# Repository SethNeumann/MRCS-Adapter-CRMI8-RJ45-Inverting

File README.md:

# REPO NAME: EagleTemplate-new
## License: Creative Commons Attribution-NonCommercial-ShareAlike

The improved CMRI8-RJ45 adapter (with limiting resistor pads) AND an inverter

This version is aimed at CMRI users using common cathode signals and a logic true output.
It includes a 74HC540 octal latch inverter (but the latches are hardwared on) to source 
~ 8 mA @ 4V, which should be adequate for modern LEDs.  Other versions of 74xx540 will 
probably work as well as 74xx541 (non inverting) although I haven't tested them.

John Plocher did the original design based on a request from Jay Beckham, and later extended
it to support limiting resistors based on user requests.  Kris Puccinelli modified this 
design to include an octal inverter, but not on EAGLE.  This is an EAGLE version, designed
for panelization.

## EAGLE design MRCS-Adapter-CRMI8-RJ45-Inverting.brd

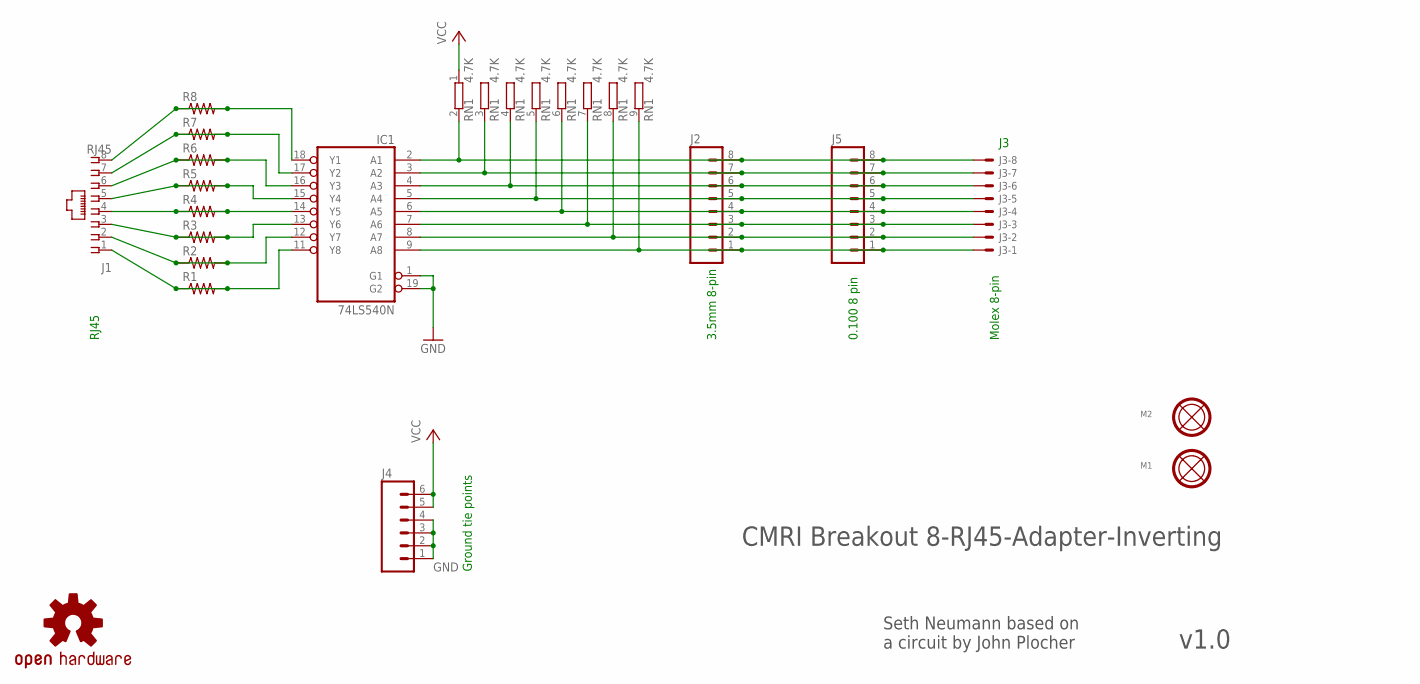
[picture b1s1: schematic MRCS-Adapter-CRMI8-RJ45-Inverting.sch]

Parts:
IC1: 74LS540N; DIL20
J1: RJ45; RJ45-NO-SHIELD
J2: CONNECTOR-M083.5MM-8; SCREWTERMINAL-3.5MM-8
J3: KK-156-8F; KK-156-8-F
J4: CONNECTOR-M06LOCK; 1X06_LOCK
J5: CONNECTOR-M08LOCK; 1X08_LOCK
M1, M2: MOUNTINGHOLE
R1, R2, R3, R4, R5, R6, R7, R8: RPTH04; AXIAL-0.4-RES
RN1: 4.7K; SIL9
U$1: DOC-OSHW-LOGO-L; OSHW-LOGO-L

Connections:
GND: IC1.1 (G1), IC1.10 (GND), IC1.19 (G2), J4.1, J4.2, J4.3, J4.4
L1: IC1.9 (A8), J2.1, J3.1, J5.1, RN1.9 (2)
L2: IC1.8 (A7), J2.2, J3.2, J5.2, RN1.8 (2)
L3: IC1.7 (A6), J2.3, J3.3, J5.3, RN1.7 (2)
L4: IC1.6 (A5), J2.4, J3.4, J5.4, RN1.6 (2)
L5: IC1.5 (A4), J2.5, J3.5, J5.5, RN1.5 (2)
L6: IC1.4 (A3), J2.6, J3.6, J5.6, RN1.4 (2)
L7: IC1.3 (A2), J2.7, J3.7, J5.7, RN1.3 (2)
L8: IC1.2 (A1), J2.8, J3.8, J5.8, RN1.2
unnamed: IC1.18 (Y1), J1.8, R8.P$1 (1), R8.P$2 (2)
unnamed: IC1.17 (Y2), J1.7, R7.P$1 (1), R7.P$2 (2)
unnamed: IC1.16 (Y3), J1.6, R6.P$1 (1), R6.P$2 (2)
unnamed: IC1.15 (Y4), J1.5, R5.P$1 (1), R5.P$2 (2)
unnamed: IC1.14 (Y5), J1.4, R4.P$1 (1), R4.P$2 (2)
unnamed: IC1.13 (Y6), J1.3, R3.P$1 (1), R3.P$2 (2)
unnamed: IC1.12 (Y7), J1.2, R2.P$1 (1), R2.P$2 (2)
unnamed: IC1.11 (Y8), J1.1, R1.P$1 (1), R1.P$2 (2)
VCC: IC1.20 (VCC), J4.5, J4.6, RN1.1

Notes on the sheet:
Molex 8-pin
3.5mm 8-pin
RJ45
v1.0
Ground tie points
CMRI Breakout 8-RJ45-Adapter-Inverting
Seth Neumann based on a circuit by John Plocher
0.100 8 pin

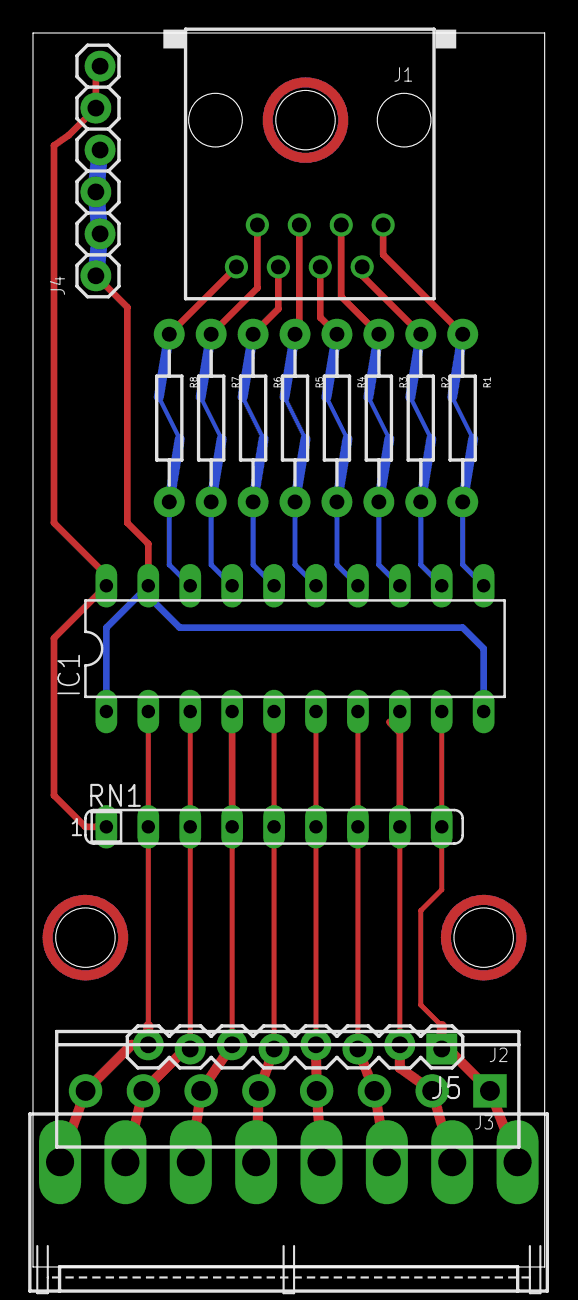
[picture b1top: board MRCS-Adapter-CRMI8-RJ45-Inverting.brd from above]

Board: 2 copper layers, 31.0 x 74.8 mm, 21 parts (0 on the bottom side), 18 nets.

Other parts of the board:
M3: MOUNTINGHOLE
U$2: CA-PROP65WARNING
U$3: MRCSLOGOBTM

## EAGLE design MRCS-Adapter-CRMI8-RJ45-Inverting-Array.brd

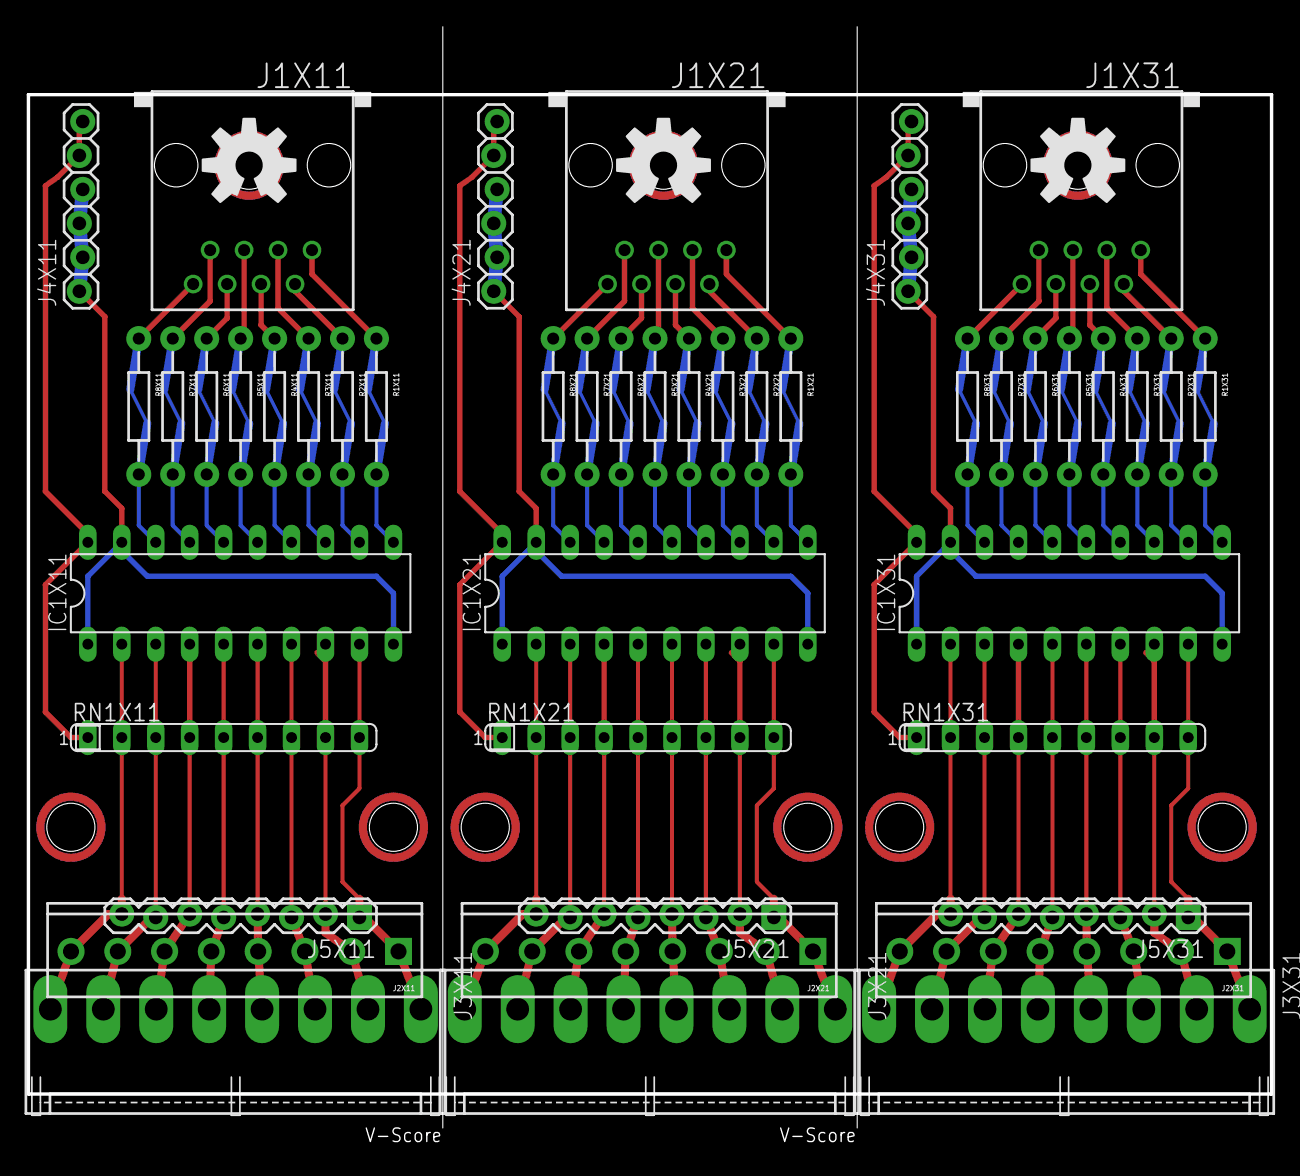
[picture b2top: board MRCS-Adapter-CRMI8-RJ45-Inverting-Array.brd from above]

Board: 2 copper layers, 93.0 x 74.8 mm, 60 parts (0 on the bottom side), 54 nets.

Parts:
IC1X11, IC1X21, IC1X31: 74LS540N; DIL20
J1X11, J1X21, J1X31: RJ45; RJ45-NO-SHIELD
J2X11, J2X21, J2X31: SCREWTERMINAL-3.5MM-8
J3X11, J3X21, J3X31: KK-156-8-F
J4X11, J4X21, J4X31: 1X06_LOCK
J5X11, J5X21, J5X31: 1X08_LOCK
M1X11, M1X21, M1X31, M2X11, M2X21, M2X31, M3X11, M3X21, M3X31: MOUNTINGHOLE
R1X11, R1X21, R1X31, R2X11, R2X21, R2X31, R3X11, R3X21, R3X31, R4X11, R4X21, R4X31, R5X11, R5X21, R5X31, R6X11, R6X21, R6X31, R7X11, R7X21, R7X31, R8X11, R8X21, R8X31: AXIAL-0.4-RES
RN1X11, RN1X21, RN1X31: 4.7K; SIL9
U$1X11, U$1X21, U$1X31: DOC-OSHW-LOGO-L; OSHW-LOGO-L
U$2X11, U$2X21, U$2X31: CA-PROP65WARNING

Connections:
GNDX11: IC1X11.1, IC1X11.10, IC1X11.19, J4X11.1, J4X11.2, J4X11.3, J4X11.4
GNDX21: IC1X21.1, IC1X21.10, IC1X21.19, J4X21.1, J4X21.2, J4X21.3, J4X21.4
GNDX31: IC1X31.1, IC1X31.10, IC1X31.19, J4X31.1, J4X31.2, J4X31.3, J4X31.4
L1X11: IC1X11.9, J2X11.1, J3X11.1, J5X11.1, RN1X11.9
L1X21: IC1X21.9, J2X21.1, J3X21.1, J5X21.1, RN1X21.9
L1X31: IC1X31.9, J2X31.1, J3X31.1, J5X31.1, RN1X31.9
L2X11: IC1X11.8, J2X11.2, J3X11.2, J5X11.2, RN1X11.8
L2X21: IC1X21.8, J2X21.2, J3X21.2, J5X21.2, RN1X21.8
L2X31: IC1X31.8, J2X31.2, J3X31.2, J5X31.2, RN1X31.8
L3X11: IC1X11.7, J2X11.3, J3X11.3, J5X11.3, RN1X11.7
L3X21: IC1X21.7, J2X21.3, J3X21.3, J5X21.3, RN1X21.7
L3X31: IC1X31.7, J2X31.3, J3X31.3, J5X31.3, RN1X31.7
L4X11: IC1X11.6, J2X11.4, J3X11.4, J5X11.4, RN1X11.6
L4X21: IC1X21.6, J2X21.4, J3X21.4, J5X21.4, RN1X21.6
L4X31: IC1X31.6, J2X31.4, J3X31.4, J5X31.4, RN1X31.6
L5X11: IC1X11.5, J2X11.5, J3X11.5, J5X11.5, RN1X11.5
L5X21: IC1X21.5, J2X21.5, J3X21.5, J5X21.5, RN1X21.5
L5X31: IC1X31.5, J2X31.5, J3X31.5, J5X31.5, RN1X31.5
L6X11: IC1X11.4, J2X11.6, J3X11.6, J5X11.6, RN1X11.4
L6X21: IC1X21.4, J2X21.6, J3X21.6, J5X21.6, RN1X21.4
L6X31: IC1X31.4, J2X31.6, J3X31.6, J5X31.6, RN1X31.4
L7X11: IC1X11.3, J2X11.7, J3X11.7, J5X11.7, RN1X11.3
L7X21: IC1X21.3, J2X21.7, J3X21.7, J5X21.7, RN1X21.3
L7X31: IC1X31.3, J2X31.7, J3X31.7, J5X31.7, RN1X31.3
L8X11: IC1X11.2, J2X11.8, J3X11.8, J5X11.8, RN1X11.2
L8X21: IC1X21.2, J2X21.8, J3X21.8, J5X21.8, RN1X21.2
L8X31: IC1X31.2, J2X31.8, J3X31.8, J5X31.8, RN1X31.2
unnamed: IC1X11.18, J1X11.8, R8X11.P$1, R8X11.P$2
unnamed: IC1X21.18, J1X21.8, R8X21.P$1, R8X21.P$2
unnamed: IC1X31.18, J1X31.8, R8X31.P$1, R8X31.P$2
unnamed: IC1X11.17, J1X11.7, R7X11.P$1, R7X11.P$2
unnamed: IC1X21.17, J1X21.7, R7X21.P$1, R7X21.P$2
unnamed: IC1X31.17, J1X31.7, R7X31.P$1, R7X31.P$2
unnamed: IC1X11.16, J1X11.6, R6X11.P$1, R6X11.P$2
unnamed: IC1X21.16, J1X21.6, R6X21.P$1, R6X21.P$2
unnamed: IC1X31.16, J1X31.6, R6X31.P$1, R6X31.P$2
unnamed: IC1X11.15, J1X11.5, R5X11.P$1, R5X11.P$2
unnamed: IC1X21.15, J1X21.5, R5X21.P$1, R5X21.P$2
unnamed: IC1X31.15, J1X31.5, R5X31.P$1, R5X31.P$2
unnamed: IC1X11.14, J1X11.4, R4X11.P$1, R4X11.P$2
unnamed: IC1X21.14, J1X21.4, R4X21.P$1, R4X21.P$2
unnamed: IC1X31.14, J1X31.4, R4X31.P$1, R4X31.P$2
unnamed: IC1X11.13, J1X11.3, R3X11.P$1, R3X11.P$2
unnamed: IC1X21.13, J1X21.3, R3X21.P$1, R3X21.P$2
unnamed: IC1X31.13, J1X31.3, R3X31.P$1, R3X31.P$2
unnamed: IC1X11.12, J1X11.2, R2X11.P$1, R2X11.P$2
unnamed: IC1X21.12, J1X21.2, R2X21.P$1, R2X21.P$2
unnamed: IC1X31.12, J1X31.2, R2X31.P$1, R2X31.P$2
unnamed: IC1X11.11, J1X11.1, R1X11.P$1, R1X11.P$2
unnamed: IC1X21.11, J1X21.1, R1X21.P$1, R1X21.P$2
unnamed: IC1X31.11, J1X31.1, R1X31.P$1, R1X31.P$2
VCCX11: IC1X11.20, J4X11.5, J4X11.6, RN1X11.1
VCCX21: IC1X21.20, J4X21.5, J4X21.6, RN1X21.1
VCCX31: IC1X31.20, J4X31.5, J4X31.6, RN1X31.1

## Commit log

2020-11-21 initial commit
    initial commit
2020-11-22 upload starting copy from non-inverting design
    starting from older design
2020-11-22 First pass at modifying the CMRI8-RJ45 adapter
    remove the frog power, add the 74HC540 and Vcc (+5) and GND
2020-11-22 added 74LS540, modified connectors
    Added inverter (74LS540), removed frog connector, added Vcc, Gnd for logic supply
2020-11-22 fixed ground trace
    Missing ground trace.
2020-11-23 various adjustments
    minor board layout adjustments
2020-11-24 final changes for panelizing
    clean up to facilitate the panelizer
2020-12-03 first production version
    Inverting version of RJ45 adapter originally designed by John Plocher for Jay Beckham. Later added limiting resistors, Kris Puccinelli asked for an inverting version
2020-12-03 Update DESCRIPTION
2020-12-13 Documentation
    rec 0.2 review by Kris Puccinelli
2020-12-13 derivative file, should not be in Git
    removed derivative file
2020-12-14 minor edits for clarity
    Kris P was kind enough to review, These are largely his suggestions.
2020-12-14 minor formatting issues in TOC
    fixed random outdents caused bu table update and subsection numbering
2020-12-20 label changes for legibility
    label changes for legibility
2020-12-24 Minor label changes
    the Claifornia Prop 65 warning covered the cuttable links under the limiting resistor pads, so I moved them and deleted some of John's SPCoast comments. It is important that the user can see the link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
2021-01-01 Changes in silk screen
    Changes in silk screen
2021-01-01 product is released
    product status is released

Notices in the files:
parts and their libraries:
SPCoast: http://freedomdefined.org/OSHW Creative Commons - Attribution - ShareAlike 3.0
